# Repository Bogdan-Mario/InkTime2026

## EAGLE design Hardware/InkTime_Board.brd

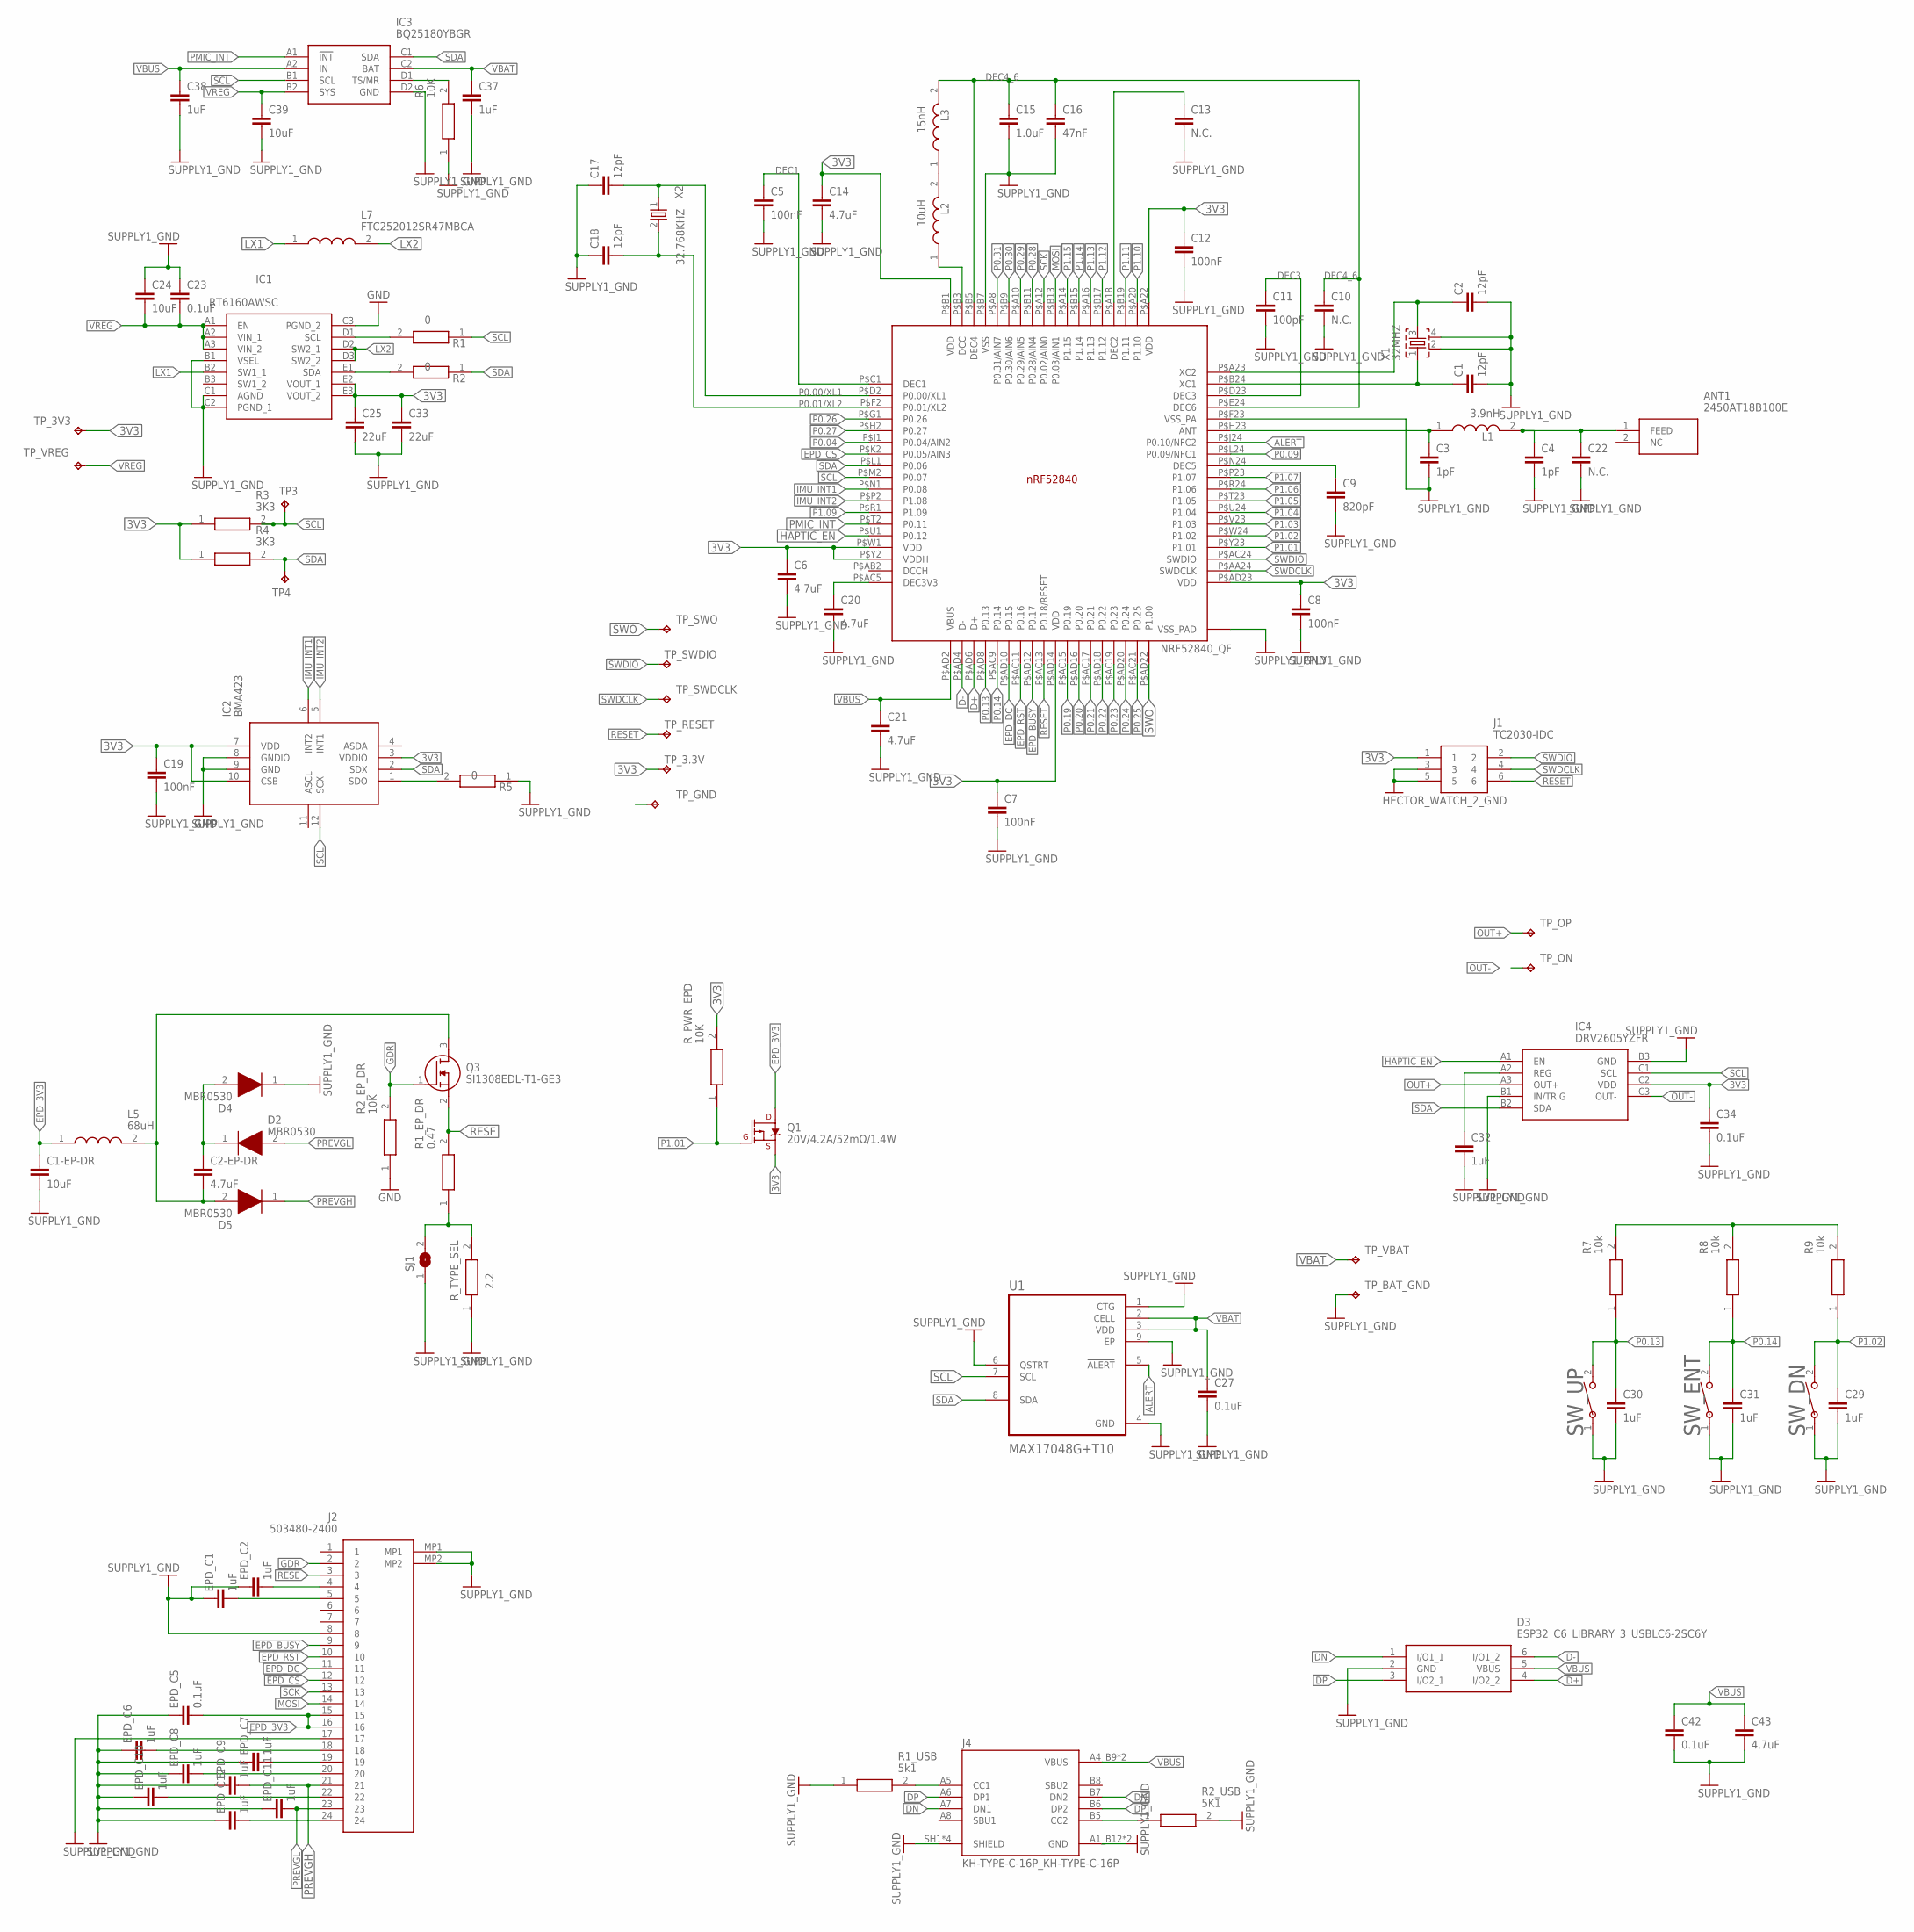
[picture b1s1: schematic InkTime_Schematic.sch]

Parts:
ANT1: 2450AT18B100E; 2450AT18B100E_ANTC3216X140N
C1, C2, C17, C18: 12pF; NORDIC_NRF_3_RESC0201_L
C1-EP-DR, C24, C39: 10uF; NORDIC_NRF_3_RESC0402_L
C2-EP-DR, C6, C14, C20, C21, C43: 4.7uF; NORDIC_NRF_3_RESC0402_L
C3, C4: 1pF; NORDIC_NRF_3_RESC0201_L
C5, C7, C8, C12, C19: 100nF; NORDIC_NRF_3_RESC0201_L
C9: 820pF; NORDIC_NRF_3_RESC0201_L
C10, C13, C22: N.C.; NORDIC_NRF_3_RESC0201_L
C11: 100pF; NORDIC_NRF_3_RESC0201_L
C15: 1.0uF; NORDIC_NRF_3_RESC0402_L
C16: 47nF; NORDIC_NRF_3_RESC0201_L
C23, C27, C34, C42: 0.1uF; NORDIC_NRF_3_RESC0201_L
C25, C33: 22uF; NORDIC_NRF_3_RESC0402_L
C29, C30, C31, C32, C37, C38: 1uF; NORDIC_NRF_3_RESC0402_L
D2, D4, D5: MBR0530; ESP32_C6_LIBRARY_5_SOD3716X135N
D3: ESP32_C6_LIBRARY_3_USBLC6-2SC6Y; ESP32_C6_LIBRARY_3_SOT95P280X145-6N
EPD_C1, EPD_C2, EPD_C6, EPD_C7, EPD_C8, EPD_C9, EPD_C10, EPD_C11, EPD_C12: 1uF; NORDIC_NRF_3_RESC0402_L
EPD_C5: 0.1uF; NORDIC_NRF_3_RESC0201_L
IC1: RT6160AWSC; RT6160AWSC_BGA15C40P3X5_140X230X60
IC2: BMA423; BMA423_BMA423
IC3: BQ25180YBGR; BQ25180YBGR_BGA8C40P2X4_100X155X50
IC4: DRV2605YZFR; DRV2605YZFR_BGA9C50P3X3_144X144X62
J1: TC2030-IDC; TC2030-IDC_TC2030IDC
J2: 503480-2400; 503480-2400_5034802400
J4: KH-TYPE-C-16P_KH-TYPE-C-16P; KH-TYPE-C-16P_KINGHELM_KH-TYPE-C-16P
L1: 3.9nH; MLP2016SR47MT0S1_INDC2016X100N
L2: 10uH; MLP2016SR47MT0S1_INDC2016X100N
L3: 15nH; MLP2016SR47MT0S1_INDC2016X100N
L5: 68uH; MLP2016SR47MT0S1_INDC2016X100N
L7: FTC252012SR47MBCA; MLP2016SR47MT0S1_INDC2016X100N
NRF52840_QF: NRF52840_QF; NORDIC_NRF_4_AQFN50P700X700X85_HS-74N
Q1: 20V/4.2A/52mΩ/1.4W; ESP32_C6_LIBRARY_4_ESP32_C6_LIBRARY_4_ESP32_C6_LIBRARY_4_ES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
Q3: SI1308EDL-T1-GE3; ESP32_C6_LIBRARY_6_SOT65P210X110-3N
R1, R2, R5: 0; CPF0201D7K68C1_0201
R1_EP_DR: 0.47; CPF0201D7K68C1_0201
R1_USB: 5k1; CPF0201D7K68C1_0201
R2_EP_DR, R6: 10K; CPF0201D7K68C1_0201
R2_USB: 5K1; CPF0201D7K68C1_0201
R3, R4: 3K3; CPF0201D7K68C1_0201
R7, R8, R9: 10k; CPF0201D7K68C1_0201
R_PWR_EPD: 10K; CPF0201D7K68C1_0201
R_TYPE_SEL: 2.2; CPF0201D7K68C1_0201
SJ1: ESP32_C6_LIBRARY_7_JUMPER_SJ
SW_DN: EVP-AKE31A_PAN; 2025-10-22_07-23-44_LIBRARY_SW_EVP-AKE31A_PAN
SW_ENT: EVP-AKE31A_PAN; 2025-10-22_07-23-44_LIBRARY_SW_EVP-AKE31A_PAN
SW_UP: EVP-AKE31A_PAN; 2025-10-22_07-23-44_LIBRARY_SW_EVP-AKE31A_PAN
TP3, TP4: HECTOR_WATCH_1_TPTP20R; HECTOR_WATCH_1_TP20R
TP_3.3V, TP_3V3: HECTOR_WATCH_1_TPTP20R; HECTOR_WATCH_1_TP20R
TP_BAT_GND: HECTOR_WATCH_1_TPTP20R; HECTOR_WATCH_1_TP20R
TP_GND: HECTOR_WATCH_1_TPTP20R; HECTOR_WATCH_1_TP20R
TP_ON: HECTOR_WATCH_1_TPTP20R; HECTOR_WATCH_1_TP20R
TP_OP: HECTOR_WATCH_1_TPTP20R; HECTOR_WATCH_1_TP20R
TP_RESET: HECTOR_WATCH_1_TPTP20R; HECTOR_WATCH_1_TP20R
TP_SWDCLK: HECTOR_WATCH_1_TPTP20R; HECTOR_WATCH_1_TP20R
TP_SWDIO: HECTOR_WATCH_1_TPTP20R; HECTOR_WATCH_1_TP20R
TP_SWO: HECTOR_WATCH_1_TPTP20R; HECTOR_WATCH_1_TP20R
TP_VBAT: HECTOR_WATCH_1_TPTP20R; HECTOR_WATCH_1_TP20R
TP_VREG: HECTOR_WATCH_1_TPTP20R; HECTOR_WATCH_1_TP20R
U1: MAX17048G+T10; ESP32_C6_LIBRARY_SON50P200X200X80-9N
X1: 32MHZ; NORDIC_NRF_BT-XTAL_2016_N
X2: 32.768KHZ; NORDIC_NRF_1_XTAL_3215_N

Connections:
3V3: C7.1, C8.1, C12.1, C14.1, C19.1, C34.1, IC2.3 (VDDIO), IC2.7 (VDD), IC2.10 (CSB), IC4.C2 (VDD), J1.1, NRF52840_QF.P$A22 (VDD), NRF52840_QF.P$AD14 (VDD), NRF52840_QF.P$AD23 (VDD), NRF52840_QF.P$B1 (VDD), Q1.2 (S), R_PWR_EPD.2, TP_3.3V.TP, TP_3V3.TP
ALERT: NRF52840_QF.P$J24 (P0.10/NFC2), U1.5 (!ALERT)
D+: D3.4 (I/O2_2), NRF52840_QF.P$AD6 (D+)
D-: D3.6 (I/O1_2), NRF52840_QF.P$AD4 (D-)
DEC1: C5.1, NRF52840_QF.P$C1 (DEC1)
DEC3: C11.1, NRF52840_QF.P$D23 (DEC3)
DEC4_6: C10.1, C15.1, C16.1, L3.2, NRF52840_QF.P$B5 (DEC4), NRF52840_QF.P$E24 (DEC6)
DN: D3.1 (I/O1_1), J4.A7 (DN1), J4.B7 (DN2)
DP: D3.3 (I/O2_1), J4.A6 (DP1), J4.B6 (DP2)
EPD_3V3: C1-EP-DR.1, EPD_C5.2, J2.15, J2.16, L5.1, Q1.3 (D)
EPD_BUSY: J2.9, NRF52840_QF.P$AD12 (P0.17)
EPD_CS: J2.12, NRF52840_QF.P$K2 (P0.05/AIN3)
EPD_DC: J2.11, NRF52840_QF.P$AD10 (P0.15)
EPD_RST: J2.10, NRF52840_QF.P$AC11 (P0.16)
GDR: J2.2, Q3.1 (G), R2_EP_DR.2
GND: C1.2, C1-EP-DR.2, C2.2, C3.2, C4.2, C5.2, C6.2, C7.2, C8.2, C9.2, C10.2, C11.2, C12.2, C13.2, C14.2, C15.2, C16.2, C17.1, C18.1, C19.2, C20.2, C21.2, C22.2, C23.1, C24.1, C25.2, C27.2, C29.2, C30.2, C31.2, C32.2, C33.2, C34.2, C37.2, C38.2, C39.2, C42.2, C43.2, D3.2 (GND), D4.1 (K), EPD_C1.1, EPD_C2.1, EPD_C5.1, EPD_C6.1, EPD_C7.1, EPD_C8.1, EPD_C9.1, EPD_C10.1, EPD_C11.1, EPD_C12.1, IC1.B1 (VSEL), IC1.C1 (AGND), IC1.C2 (PGND_1), IC1.C3 (PGND_2), IC2.8 (GNDIO), IC2.9 (GND), IC3.D2 (GND), IC4.B1 (IN/TRIG), IC4.B3 (GND), J1.3, J1.5, J2.8, J2.17, J2.MP1, J2.MP2, J4.A1_B12 (GND), J4.A12_B1 (GND), J4.SH1 (SHIELD), J4.SH2 (SHIELD), J4.SH3 (SHIELD), J4.SH4 (SHIELD), NRF52840_QF.P$74 (VSS_PAD), NRF52840_QF.P$75 (VSS_PAD), NRF52840_QF.P$76 (VSS_PAD), NRF52840_QF.P$77 (VSS_PAD), NRF52840_QF.P$78 (VSS_PAD), NRF52840_QF.P$79 (VSS_PAD), NRF52840_QF.P$80 (VSS_PAD), NRF52840_QF.P$81 (VSS_PAD), NRF52840_QF.P$82 (VSS_PAD), NRF52840_QF.P$83 (VSS_PAD), NRF52840_QF.P$84 (VSS_PAD), NRF52840_QF.P$85 (VSS_PAD), NRF52840_QF.P$86 (VSS_PAD), NRF52840_QF.P$87 (VSS_PAD), NRF52840_QF.P$88 (VSS_PAD), NRF52840_QF.P$89 (VSS_PAD), NRF52840_QF.P$90 (VSS_PAD), NRF52840_QF.P$B7 (VSS), NRF52840_QF.P$F23 (VSS_PA), R1_USB.1, R2_EP_DR.1, R2_USB.2, R5.1, R6.1, R_TYPE_SEL.1, SJ1.1, SW_DN.1, SW_ENT.1, SW_UP.1, TP_BAT_GND.TP, U1.1 (CTG), U1.4 (GND), U1.6 (QSTRT), U1.9 (EP), X1.2, X1.4
HAPTIC_EN: IC4.A1 (EN), NRF52840_QF.P$U1 (P0.12)
IMU_INT1: IC2.6 (INT2), NRF52840_QF.P$N1 (P0.08)
IMU_INT2: IC2.5 (INT1), NRF52840_QF.P$P2 (P1.08)
LX1: IC1.B2 (SW1_1), L7.1
LX2: IC1.D2 (SW2_1), IC1.D3 (SW2_2), L7.2
MOSI: J2.14, NRF52840_QF.P$B13 (P0.03/AIN1)
unnamed: C1.1, NRF52840_QF.P$B24 (XC1), X1.1
unnamed: ANT1.1 (FEED), C4.1, C22.1, L1.2
unnamed: C3.1, L1.1, NRF52840_QF.P$H23 (ANT)
unnamed: C2.1, NRF52840_QF.P$A23 (XC2), X1.3
unnamed: C6.1, NRF52840_QF.P$W1 (VDD), NRF52840_QF.P$Y2 (VDDH)
unnamed: C20.1, NRF52840_QF.P$AC5 (DEC3V3)
unnamed: C13.1, NRF52840_QF.P$A18 (DEC2)
unnamed: L2.1, NRF52840_QF.P$B3 (DCC)
unnamed: L2.2, L3.1
unnamed: IC1.D1 (SCL), R1.2
unnamed: IC1.E1 (SDA), R2.2
unnamed: C9.1, NRF52840_QF.P$N24 (DEC5)
unnamed: C25.1, C33.1, IC1.E2 (VOUT_1), IC1.E3 (VOUT_2)
unnamed: R3.1, R4.1
unnamed: C2-EP-DR.1, D2.1 (K), D4.2 (A)
unnamed: IC2.1 (SDO), R5.2
unnamed: C2-EP-DR.2, D5.2 (A), L5.2, Q3.3 (D)
unnamed: IC3.D1 (TS/MR), R6.2
unnamed: R1_EP_DR.1, R_TYPE_SEL.2, SJ1.2
unnamed: C32.1, IC4.A2 (REG)
unnamed: R7.2, R8.2, R9.2
unnamed: J4.A5 (CC1), R1_USB.2
unnamed: EPD_C12.2, J2.24
unnamed: EPD_C2.2, J2.4
unnamed: EPD_C1.2, J2.5
unnamed: J4.B5 (CC2), R2_USB.1
unnamed: EPD_C6.2, J2.18
unnamed: EPD_C7.2, J2.19
unnamed: EPD_C8.2, J2.20
unnamed: EPD_C10.2, J2.22
OUT+: IC4.A3 (OUT+), TP_OP.TP
OUT-: IC4.C3 (OUT-), TP_ON.TP
P0.00/XL1: C17.2, NRF52840_QF.P$D2 (P0.00/XL1), X2.1
P0.01/XL2: C18.2, NRF52840_QF.P$F2 (P0.01/XL2), X2.2
P0.04: NRF52840_QF.P$J1 (P0.04/AIN2)
P0.09: NRF52840_QF.P$L24 (P0.09/NFC1)
P0.13: C30.1, NRF52840_QF.P$AD8 (P0.13), R7.1, SW_UP.2
P0.14: C31.1, NRF52840_QF.P$AC9 (P0.14), R8.1, SW_ENT.2
P0.19: NRF52840_QF.P$AC15 (P0.19)
P0.20: NRF52840_QF.P$AD16 (P0.20)
P0.21: NRF52840_QF.P$AC17 (P0.21)
P0.22: NRF52840_QF.P$AD18 (P0.22)
P0.23: NRF52840_QF.P$AC19 (P0.23)
P0.24: NRF52840_QF.P$AD20 (P0.24)
P0.25: NRF52840_QF.P$AC21 (P0.25)
P0.26: NRF52840_QF.P$G1 (P0.26)
P0.27: NRF52840_QF.P$H2 (P0.27)
P0.28: NRF52840_QF.P$B11 (P0.28/AIN4)
P0.29: NRF52840_QF.P$A10 (P0.29/AIN5)
P0.30: NRF52840_QF.P$B9 (P0.30/AIN6)
P0.31: NRF52840_QF.P$A8 (P0.31/AIN7)
P1.01: NRF52840_QF.P$Y23 (P1.01), Q1.1 (G), R_PWR_EPD.1
P1.02: C29.1, NRF52840_QF.P$W24 (P1.02), R9.1, SW_DN.2
P1.03: NRF52840_QF.P$V23 (P1.03)
P1.04: NRF52840_QF.P$U24 (P1.04)
P1.05: NRF52840_QF.P$T23 (P1.05)
P1.06: NRF52840_QF.P$R24 (P1.06)
P1.07: NRF52840_QF.P$P23 (P1.07)
P1.09: NRF52840_QF.P$R1 (P1.09)
P1.10: NRF52840_QF.P$A20 (P1.10)
P1.11: NRF52840_QF.P$B19 (P1.11)
P1.12: NRF52840_QF.P$B17 (P1.12)
P1.13: NRF52840_QF.P$A16 (P1.13)
P1.14: NRF52840_QF.P$B15 (P1.14)
P1.15: NRF52840_QF.P$A14 (P1.15)
PMIC_INT: IC3.A1 (!INT), NRF52840_QF.P$T2 (P0.11)
PREVGH: D5.1 (K), EPD_C9.2, J2.21
PREVGL: D2.2 (A), EPD_C11.2, J2.23
RESE: J2.3, Q3.2 (S), R1_EP_DR.2
RESET: J1.6, NRF52840_QF.P$AC13 (P0.18/RESET), TP_RESET.TP
SCK: J2.13, NRF52840_QF.P$A12 (P0.02/AIN0)
SCL: IC2.12 (SCX), IC3.B1 (SCL), IC4.C1 (SCL), NRF52840_QF.P$M2 (P0.07), R1.1, R3.2, TP3.TP, U1.7 (SCL)
SDA: IC2.2 (SDX), IC3.C1 (SDA), IC4.B2 (SDA), NRF52840_QF.P$L1 (P0.06), R2.1, R4.2, TP4.TP, U1.8 (SDA)
SWDCLK: J1.4, NRF52840_QF.P$AA24 (SWDCLK), TP_SWDCLK.TP
SWDIO: J1.2, NRF52840_QF.P$AC24 (SWDIO), TP_SWDIO.TP
SWO: NRF52840_QF.P$AD22 (P1.00), TP_SWO.TP
VBAT: C27.1, C37.1, IC3.C2 (BAT), TP_VBAT.TP, U1.2 (CELL), U1.3 (VDD)
VBUS: C21.1, C38.1, C42.1, C43.1, D3.5 (VBUS), IC3.A2 (IN), J4.A4_B9 (VBUS), J4.A9_B4 (VBUS), NRF52840_QF.P$AD2 (VBUS)
VREG: C23.2, C24.2, C39.1, IC1.A1 (EN), IC1.A2 (VIN_1), IC1.A3 (VIN_2), IC3.B2 (SYS), TP_VREG.TP

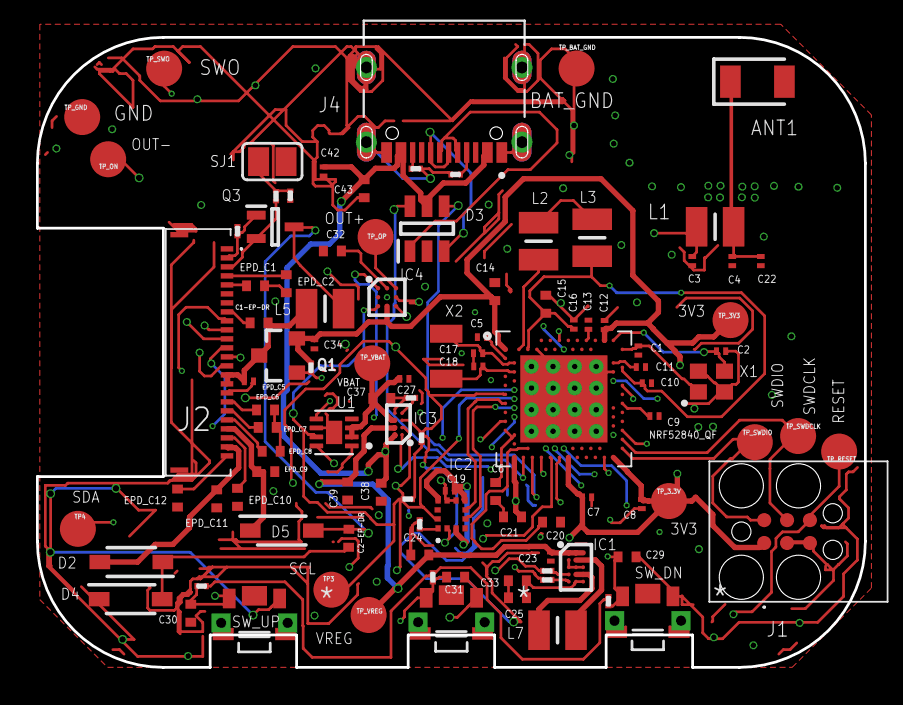
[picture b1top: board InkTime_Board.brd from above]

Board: 4 copper layers, 46.0 x 35.0 mm, 105 parts (0 on the bottom side), 74 nets.

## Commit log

2026-04-10 Proiect
2026-04-10 Add Apache License 2.0 to the project
2026-04-10 test

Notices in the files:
parts and their libraries:
COPYRIGHT: Copyright (C) 2025 Ultra Librarian. All rights reserved.
